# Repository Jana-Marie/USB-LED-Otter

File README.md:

# USB-LED-Otter
The tiny USB to adressable LED adapter that fits in your USB port :3

## Usage

    $ cd USB-LED-Otter-FW
    $ make
    $ dfu-util -a 0 -s 0x08000000:leave -D build/firmware.bin

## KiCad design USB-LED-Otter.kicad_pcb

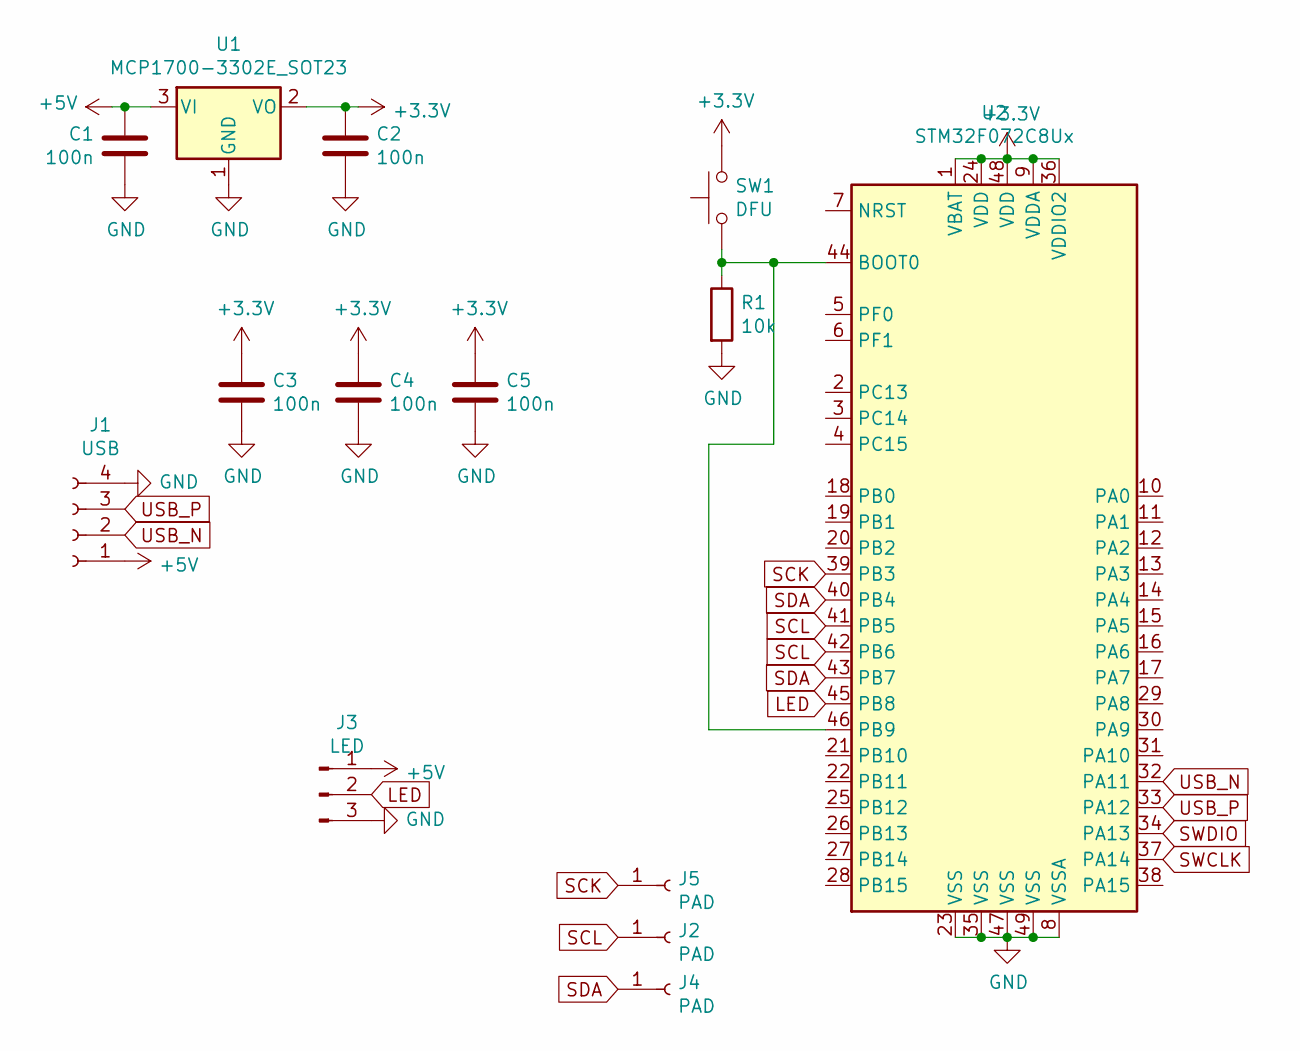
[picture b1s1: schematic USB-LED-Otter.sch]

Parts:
C1, C2, C3, C4, C5: 100n; C_0402_1005Metric
J1: USB; USBPCB
J2, J4, J5: PAD; Pad_0.80.8
J3: LED; LED-Strip
R1: 10k; R_0402_1005Metric
SW1: DFU; SW_SPST_EVQP7A
U1: MCP1700-3302E_SOT23; SOT-23
U2: STM32F072C8Ux; QFN-48-1EP_7x7mm_P0.5mm_EP2.6x2.6mm

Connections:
+3V3: C2.1, C3.1, C4.1, C5.1, SW1.2, U1.2 (VO), U2.1 (VBAT), U2.9 (VDDA), U2.24 (VDD), U2.36 (VDDIO2), U2.48 (VDD)
+5V: C1.1, J1.1, J3.1, U1.3 (VI)
GND: C1.2, C2.2, C3.2, C4.2, C5.2, J1.4, J3.3, R1.2, U1.1 (GND), U2.8 (VSSA), U2.23 (VSS), U2.35 (VSS), U2.47 (VSS), U2.49 (VSS)
LED: J3.2, U2.45 (PB8)
unnamed: R1.1, SW1.1, U2.44 (BOOT0), U2.46 (PB9)
SCK: J5.1, U2.39 (PB3)
SCL: J2.1, U2.41 (PB5), U2.42 (PB6)
SDA: J4.1, U2.40 (PB4), U2.43 (PB7)
SWCLK: U2.37 (PA14)
SWDIO: U2.34 (PA13)
USB_N: J1.2, U2.32 (PA11)
USB_P: J1.3, U2.33 (PA12)

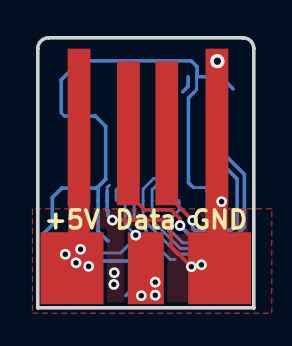
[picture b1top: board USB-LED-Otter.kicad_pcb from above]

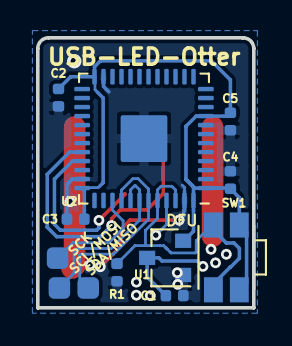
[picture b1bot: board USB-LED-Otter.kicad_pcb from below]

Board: 2 copper layers, 12.0 x 15.0 mm, 14 parts (12 on the bottom side), 10 nets.

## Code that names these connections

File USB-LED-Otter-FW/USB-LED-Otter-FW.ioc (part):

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Mcu.Name=STM32F072C(8-B)Ux
Mcu.Package=UFQFPN48
Mcu.UserName=STM32F072CBUx
PA11.Mode=Device
PA11.Signal=USB_DM
PA12.Mode=Device
PA12.Signal=USB_DP
PB8.GPIOParameters=GPIO_Speed,GPIO_Label
PB8.GPIO_Label=LED_Out
PB8.GPIO_Speed=GPIO_SPEED_FREQ_HIGH
PB8.Signal=S_TIM16_CH1
PB9.Signal=GPIO_Input
RCC.SYSCLKFreq_VALUE=48000000
RCC.SYSCLKSource=RCC_SYSCLKSOURCE_HSI48
board=custom

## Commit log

2019-11-18 added gerber+images
2019-12-13 added example code
2019-12-13 moved images
2019-12-13 remove library cache from git
2019-12-13 remove footprint cache
2019-12-13 add .gitignore via `curl https://gitignore.io/api/kicad`
2019-12-13 remove backup files
2019-12-13 Adding KiCAD-libs as submodule
2019-12-13 Adding relative paths to symbol, footprint libraries
2019-12-21 added bom
